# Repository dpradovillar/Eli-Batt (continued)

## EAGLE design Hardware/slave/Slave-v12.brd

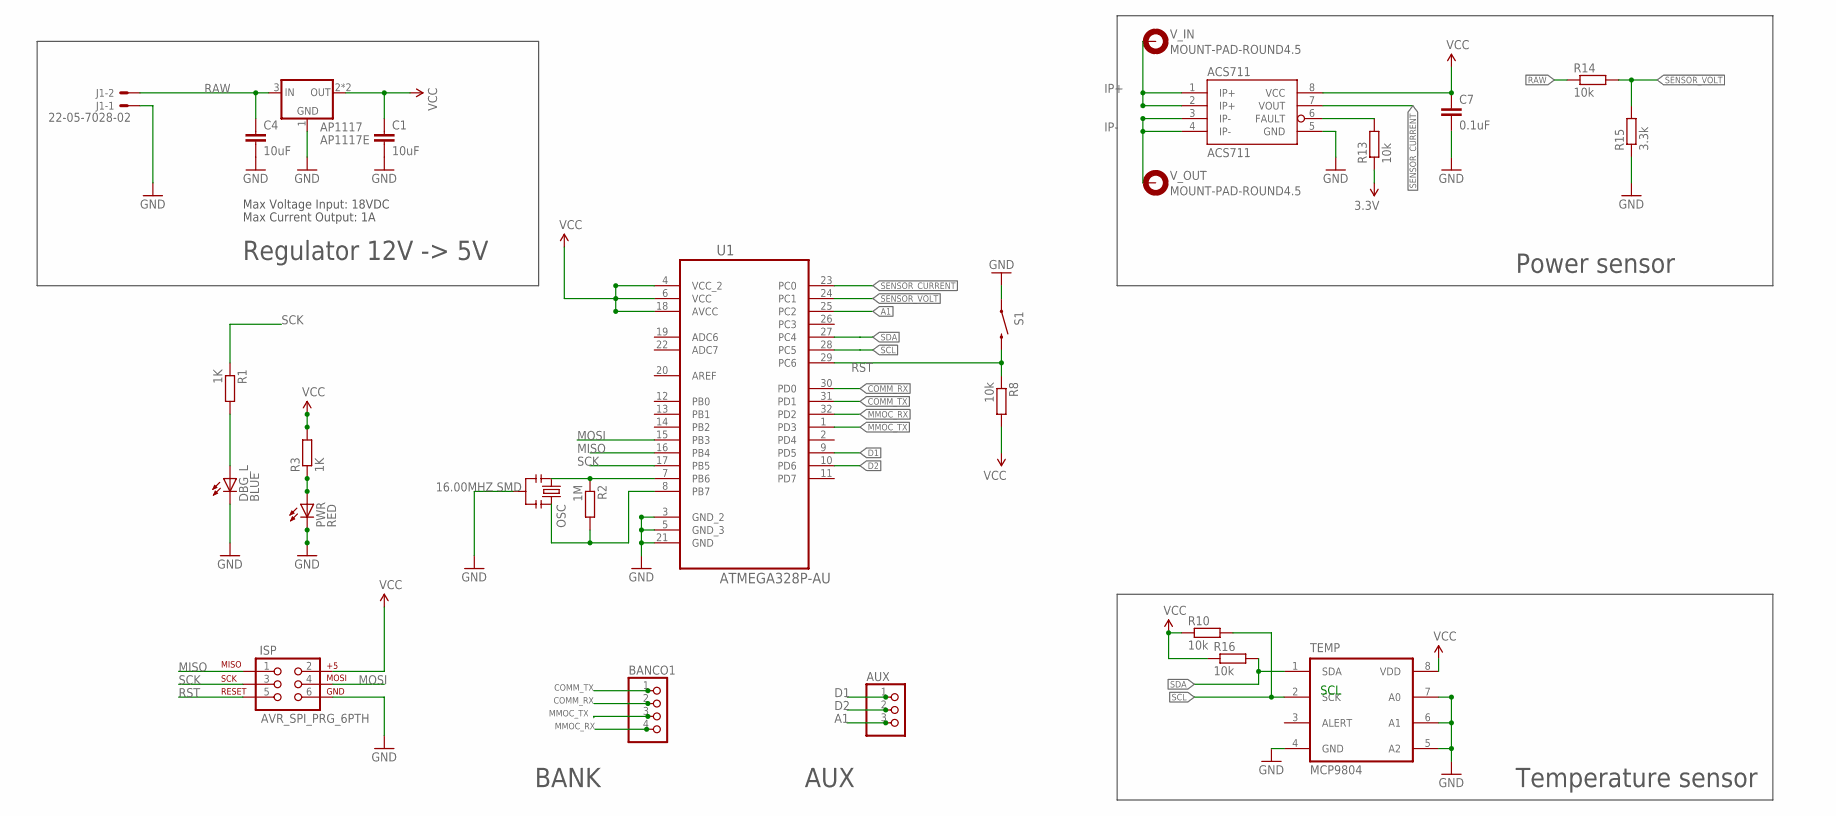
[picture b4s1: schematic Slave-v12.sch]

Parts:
ACS711: ACS711; SOIC8; MPN ACS711KLCTR-25AB-T
AP1117: AP1117E; SOT223; MPN AP1117E50G-13
AUX: PINHD-1X3; 1X03
BANCO1: PINHD-1X4; 1X04
C1, C4: 10uF; C0805K; MPN 0805ZD106KAT2A
C7: 0.1uF; C0805K; MPN MC0603B104K500CT
DBG_L: BLUE; CHIPLED_0805; MPN 150080BS75000
ISP: AVR_SPI_PRG_6PTH; 2X3
J1: 22-05-7028-02; 7395-02
OSC: 16.00MHZ SMD; RESONATOR-SMD; MPN PBRC8.00HR50X000
PWR: RED; CHIPLED_0805; MPN KPT-2012SRC-J4
R1, R3: 1K; R0805; MPN CRCW08051K00FKTA
R2: 1M; R0805; MPN CRCW080510K0FKTA
R8, R10, R13, R14, R16: 10k; R0805; MPN CRCW080510K0FKTA
R15: 3.3k; R0805; MPN CRCW08053K30FKTA
S1: SWITCH-MOMENTARY-2-SMD-1101NE; TACTILE-SWITCH-1101NE
TEMP: MCP9804; MSOP8; MPN MCP9808-E/MS
U1: ATMEGA328P-AU; QFP80P900X900X120-32N
V_IN: MOUNT-PAD-ROUND4.5; 4,5-PAD
V_OUT: MOUNT-PAD-ROUND4.5; 4,5-PAD

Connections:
A1: AUX.3, U1.25 (PC2)
COMM_RX: BANCO1.2, U1.30 (PD0)
COMM_TX: BANCO1.1, U1.31 (PD1)
D1: AUX.1, U1.9 (PD5)
D2: AUX.2, U1.10 (PD6)
GND: ACS711.5 (GND), AP1117.1 (GND), C1.2, C4.2, C7.2, DBG_L.C, ISP.6, J1.1, OSC.2, PWR.C, R15.1, S1.P$1 (1), TEMP.4 (GND), TEMP.5 (A2), TEMP.6 (A1), TEMP.7 (A0), U1.3 (GND_2), U1.5 (GND_3), U1.21 (GND)
IP+: ACS711.1 (IP+), ACS711.2 (IP+), V_IN.B4,5
IP-: ACS711.3 (IP-), ACS711.4 (IP-), V_OUT.B4,5
MISO: ISP.1, U1.16 (PB4)
MMOC_RX: U1.32 (PD2)
MMOC_TX: BANCO1.3, U1.1 (PD3)
MOSI: ISP.4, U1.15 (PB3)
unnamed: OSC.1, R2.1, U1.7 (PB6)
unnamed: DBG_L.A, R1.2
unnamed: PWR.A, R3.1
unnamed: OSC.3, R2.2, U1.8 (PB7)
unnamed: ACS711.6 (FAULT), R13.2
RAW: AP1117.3 (IN), C4.1, J1.2, R14.1
RST: ISP.5, R8.1, S1.P$2 (2), U1.29 (PC6)
SCK: ISP.3, R1.1, U1.17 (PB5)
SCL: R10.2, TEMP.2 (SCK), U1.28 (PC5)
SDA: R16.2, TEMP.1 (SDA), U1.27 (PC4)
SENSOR_CURRENT: ACS711.7 (VOUT), U1.23 (PC0)
SENSOR_VOLT: R14.2, R15.2, U1.24 (PC1)
VCC: ACS711.8 (VCC), AP1117.2 (OUT), AP1117.4 (OUT), C1.1, C7.1, ISP.2, R3.2, R8.2, R10.1, R13.1, R16.1, TEMP.8 (VDD), U1.4 (VCC_2), U1.6 (VCC), U1.18 (AVCC)

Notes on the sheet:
Max Voltage Input: 18VDC
Max Current Output: 1A
Regulator 12V -> 5V
Power sensor
Temperature sensor
SCL
BANK
AUX

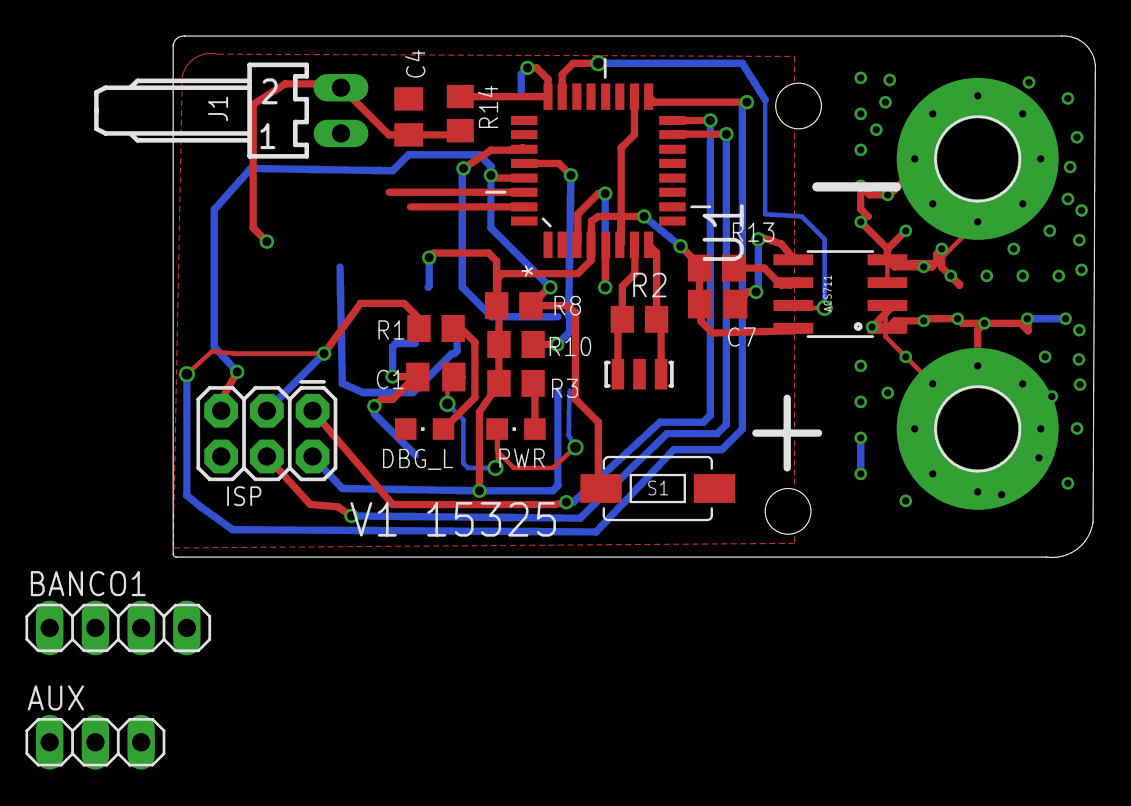
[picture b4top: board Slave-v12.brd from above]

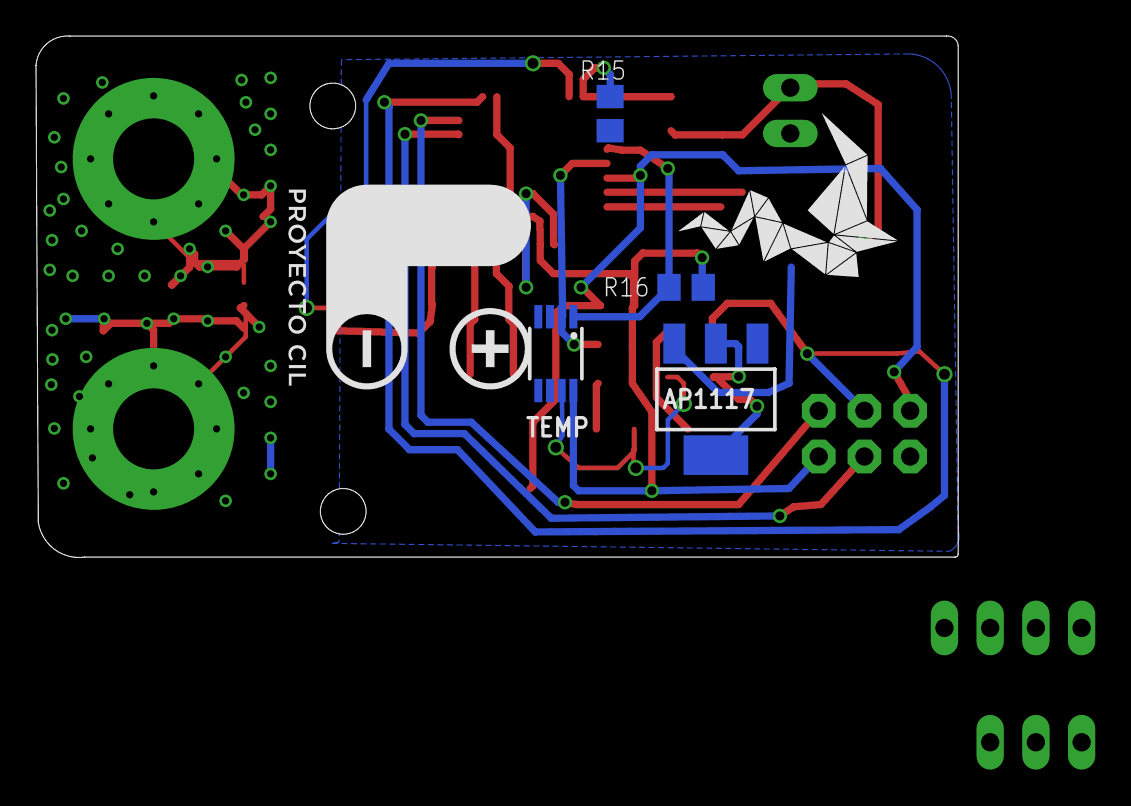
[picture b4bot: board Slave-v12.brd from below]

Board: 2 copper layers, 51.2 x 29.0 mm, 28 parts (6 on the bottom side), 24 nets.

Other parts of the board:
U$1: LOGO_CIL
U$4: LOGO_ELIBATT2

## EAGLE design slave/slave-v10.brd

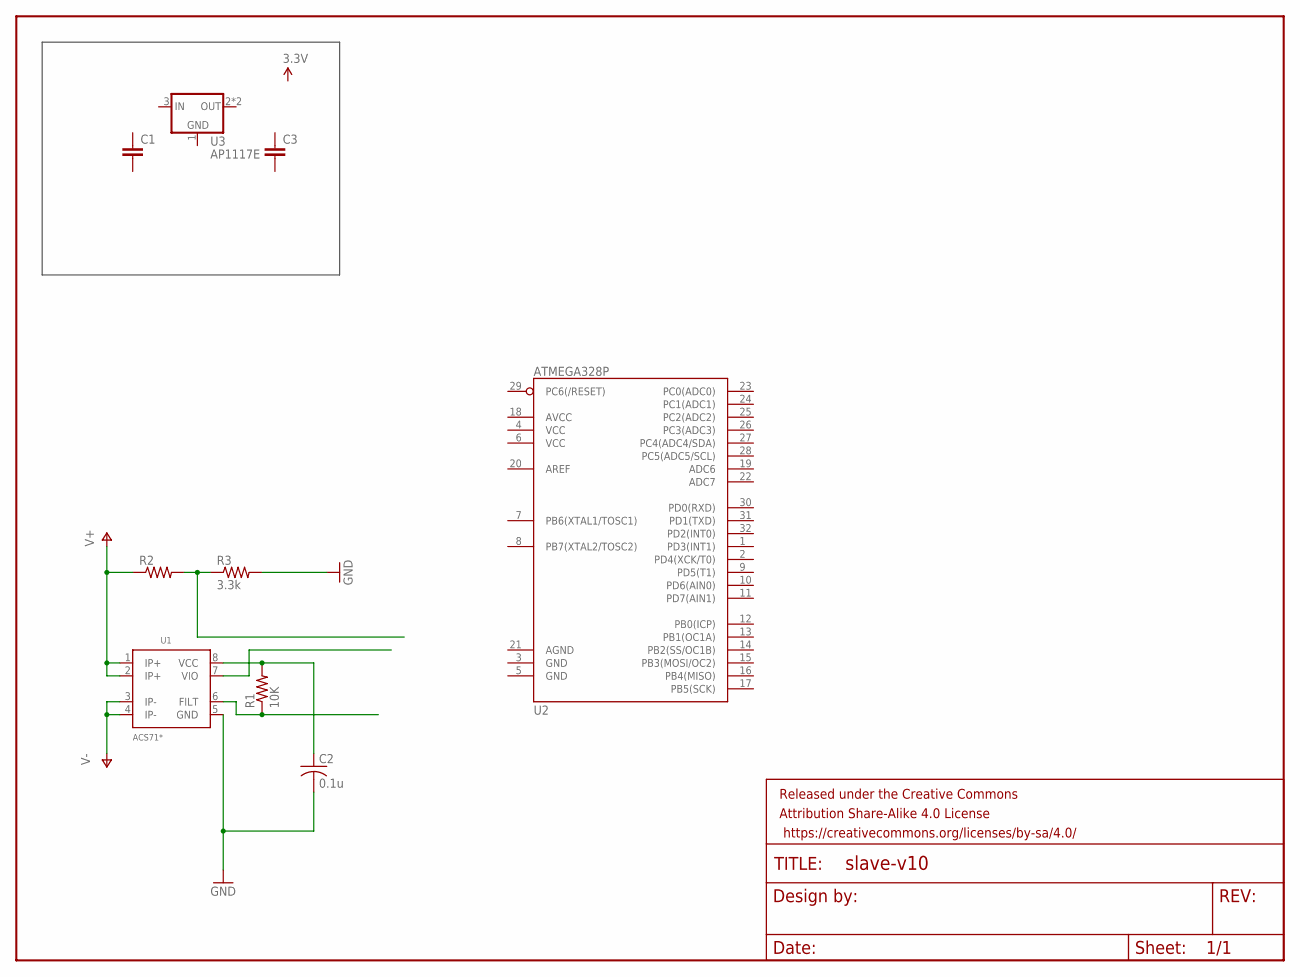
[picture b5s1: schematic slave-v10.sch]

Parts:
C1, C3: CAP0805; 0805
C2: 0.1u; C0603; PARTNO CC0603MRY5V9BB104
FRAME1: FRAME-LETTER; CREATIVE_COMMONS
R1: 10K; R0603; PARTNO RMCF0603FT10K0
R2: 10k; R0603; PARTNO ERJ-3EKF3302V
R3: 3.3k; R0603; PARTNO RMCF0603FT10K0
U1: ACS71*; SO08; PARTNO ACS715ELCTR-20A-T
U2: ATMEGA328P; TQFP32-08
U3: AP1117E; SOT223

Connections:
5V: C2.1, R1.2, U1.8 (VCC)
GND: C2.2, R3.2, U1.5 (GND)
unnamed: R1.1, U1.6 (FILT)
V+: R2.1, U1.1 (IP+), U1.2 (IP+)
V-: U1.3 (IP-), U1.4 (IP-)
VSENSE: R2.2, R3.1

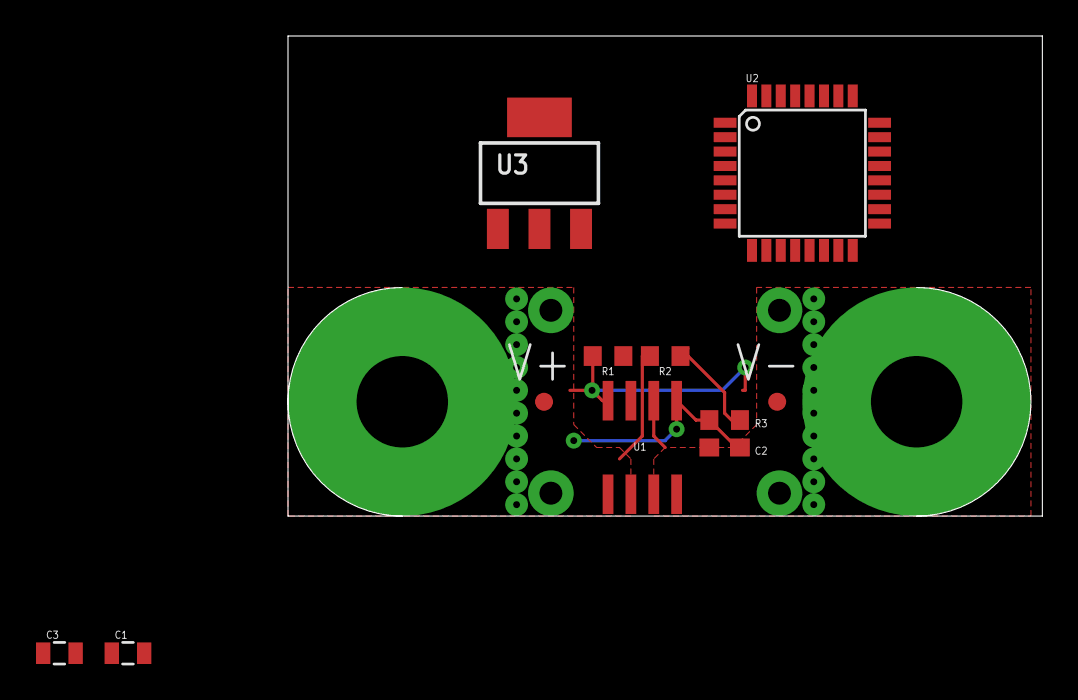
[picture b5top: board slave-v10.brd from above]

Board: 2 copper layers, 41.9 x 26.7 mm, 12 parts (0 on the bottom side), 6 nets.

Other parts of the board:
U$1, U$2: FIDUCIAL_G10

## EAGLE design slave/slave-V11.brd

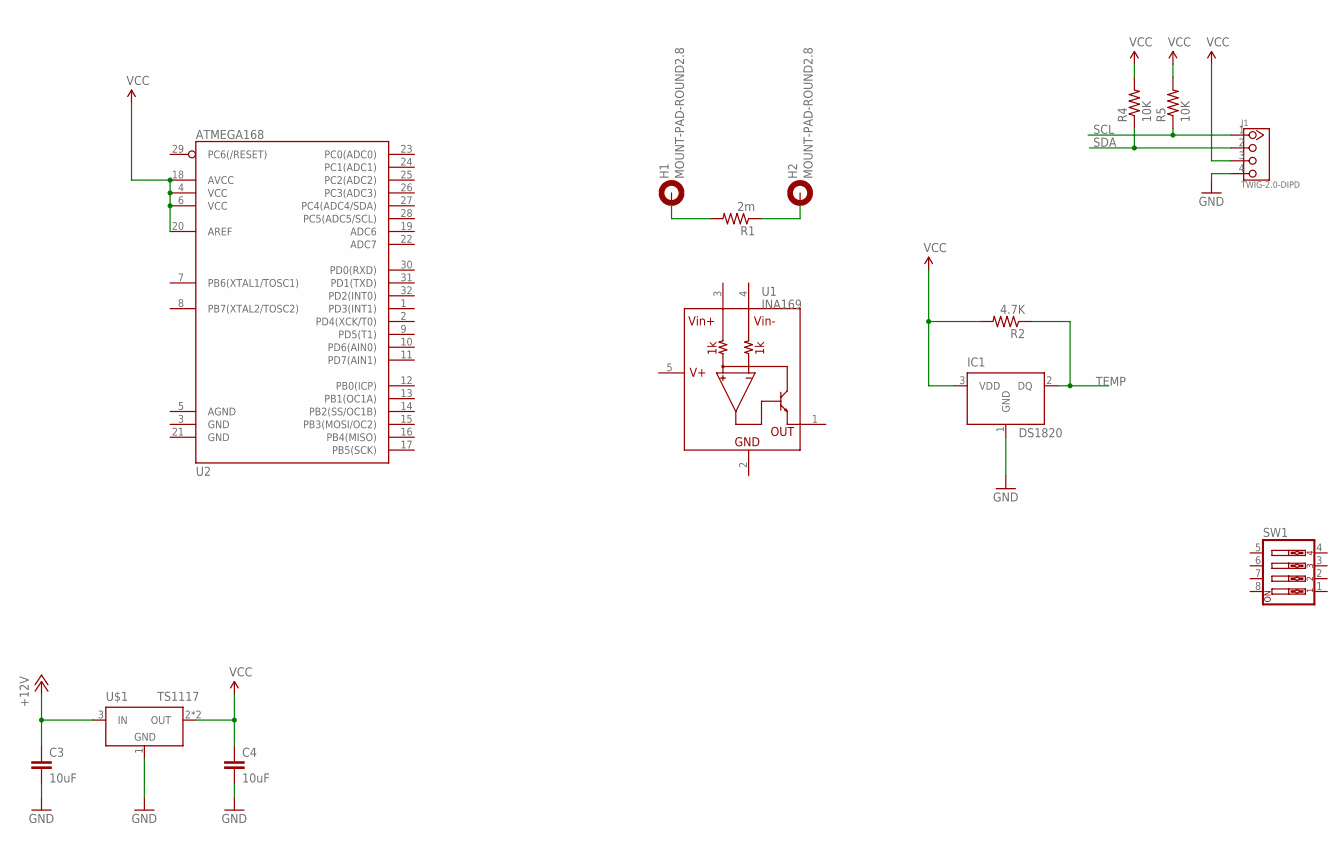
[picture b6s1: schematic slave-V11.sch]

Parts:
C3, C4: 10uF; 0805
H1, H2: MOUNT-PAD-ROUND2.8; 2,8-PAD
IC1: DS1820; TO-92
J1: TWIG-2.0-DIPD; 2.0_1X4_90
R1: 2m; R2512
R2: 4.7K; 0805
R4, R5: 10K; 0805
SW1: SW_DIP-4; EDG-04
U1: INA169; SOT23-5
U2: ATMEGA168; TQFP32-08
U$1: TS1117; SOT223

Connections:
+12V: C3.1, U$1.3 (IN)
GND: C3.2, C4.2, IC1.1 (GND), J1.4, U$1.1 (GND)
SCL: J1.1, R5.1
SDA: J1.2, R4.1
TEMP: IC1.2 (DQ), R2.1
VCC: C4.1, IC1.3 (VDD), J1.3, R2.2, R4.2, R5.2, U2.4 (VCC), U2.6 (VCC), U2.18 (AVCC), U2.20 (AREF), U$1.2 (OUT), U$1.4 (OUT)
VIN+: H1.B2,8, R1.2
VIN-: H2.B2,8, R1.1

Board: 2 copper layers, 14 parts (0 on the bottom side), 8 nets, no tracks yet.

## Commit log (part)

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2014-06-12 primer git
2014-06-12 segundo git
2014-06-12 Primer diseño PCB Slave
2014-06-27 a new master was born
2014-06-27 SD + Atmega1280 + reg5V
2014-07-01 Faltan cosas
2014-07-01 fix RESET pin
2014-07-02 Avanzado diagrama de la parte del ft232.
2014-07-02 Conector USBMini
    Es más resistente que el USBmicro mecanicamente. El usb normal exije un
    cable no tan standar
2014-07-04 todos los componentes V10
    Falta revisar compatibilidad entre modulos y hacer layout
2014-07-14 add sensor eagle lbr
2014-07-14 add grove connector eagle lbr
2014-07-14 avanzado temperatura y otros
2014-07-15 agregado comunicacion
2014-07-15 add resonator
2014-07-15 12DC Power Connector and 1st layout
2014-07-15 agregados archivos temporales al ignore list
2014-07-15 agregados pads
2014-07-15 actualizado brd, y arreglado tamaño de algunos componentes
2014-07-15 orden en esquematico
2014-07-15 some trace route
2014-07-16 more traces
2014-07-16 casi todas las pistas
    FALTA!! Revisar que no hayan circulos en circuitos de potencia y agregar
    pistas sensor corriente.
2014-07-17 archivos temp de forma generica al ignore list
2014-07-17 Corregdas pistas, corregido error en la pila del RTC
2014-07-17 modelo 3d
2014-07-17 Agrandada pista de corriente
2014-07-18 Revert "."
    This reverts commit a0e0a30c928bb4e20c64730e80fb18a043fca9c0.
2014-07-18 Ajustado silk Screen
2014-07-18 elimindos archivos inutiles
2014-07-18 Gerbers
2014-07-18 render
2014-07-22 add reset button
    and rounded corners
2014-07-22 release for manufacture
    gerbers with logo and renders
2014-07-23 fix gnd for PWR LED and update gerbers with logos
2014-07-24 gerbers fix
    add current sensor cupper area to the soldermask
2014-07-28 add AUX Current sensor
2014-07-30 Revert "."
    This reverts commit 88ed2cc015553062a76e2134231f87feefea0a33.
2014-07-31 render
    PCB Black
2014-08-02 gerbes + BOM
    add more tweaks
2014-08-30 Movido a carpeta Hardware, creada carpeta vacia Firmware
2014-08-30 Probando otro usuario
2014-08-30 Agrega estructura a carpeta Firmware.
    Se colocan librerias en carpeta libraries.
    Se crean dos scripts principales, uno para master y uno para slave.
    Se crea carpeta de pruebas, con los .ino que utilizan las librerias (similar a firmware_master y firmware_slave)
    Falta crear libreria firmware.h que contendra las definiciones de master y slave, para usar en los .ino de firmware.
2014-08-31 Agrega definicion de clases para firmware de master y slave.
    Falta agregar los metodos.
2014-08-31 Agrega librerias utilitarias para construccion de firmware.
    - Agrega EepromId, que maneja los ids unicos escritos en la eeprom de la tarjeta.
    - Agrega SampleCollector, que permite obtener datos y ejecutar acciones a uan frequencia determinada.
    - Agrega SimpleCrc, que permite construir checksums para validar contenidos de datos.
2014-08-31 Corrige readme.txt
2014-09-02 Se inician pruebas de librerias (se usan los Firmware* para este fin).
    - Se mueve SoftwareSerial a libraries (se agrega constructor vacio, por
    conveniencia para Elibatt)
    - Se agrega la nueva libreria DataExchanger para intercambio de mensajes
    entre tarjetas slave, y master/slave.
    - Se agrega libreria DataStream para envio de datos complejos.
    - Se actualiza EepromId.
2014-09-02 Se termina de implementar comunicacion para Elibatt. Faltan pruebas.
    Se completa DataExchanger.
    - Falta incluir mecanismo de timeout.
    - Falta includeir mecanismo de acknowledgement.
    - Corregido multiples bugs.
    - Falta terminar de documentar.
    - Falta manejar errores de funcionamiento (se desconecta un Slave en
2014-09-02 BOM actualizado + cambio de R en FAULT
2014-09-03 Comunicacion terminada y testeada.
    Faltan aun funcionalidades menores.
2014-09-05 Se agrega prueba de sensores analogos e i2c (temperatura).
    Se crea libreria I2cInput para manejo de sensores i2c (en particular, el de temperatura).
    Se crea libreria AnalogInput para manejo de sensores analogos (en particular, el de corriente y voltaje).
    Se agrega libreria de Adafruit modificada, dependencia de mcp9808.
2014-09-05 Se agrega version 0.1 compilada para windows. Se agregan DLLs de Qt necesarias para deploy.
2014-09-05 Se agrega proyecto Website y ServoController.
    Website es el sitio web interno j2ee para publicacion de datos y generacion de reportes.
    ServoController es un proyecto de prueba para comunicacion bluetooth-android.
2014-09-07 Agrega libreria para escribir datos a tarjeta SD (falta refactorizar e implementar).
2014-09-08 Se completan clases para escritura en SD.
    Falta volcar datos, de sensores genericos a SD.
    Se corrigen bugs menores y se agrega documentacion.
    TODO(rtapiapincheira): renombrar eepromId y agregar soporte para escribir
    otras variables en la eeprom.
2014-09-11 Se mejora comunicacion entre tarjetas esclavo/maestro.
    Se agrega software para prueba de GPS.
    Se agrega libreria Debugger para crear traza de logs.
    Se renombra EepromId a EepromWriter.
    Se comienza a implementar logica de FirmwareMaster y FirmwareSlave
    (firmwares definitivos).
    Se completa un poco mas software para configuracion de tarjetas.
2014-09-12 Se corrigen errores de include, se trabaja en protocolo master/slave.
    Falta probar.
    Se mejoran los .ino de prueba de firmware master/slave.
    Se mejora .ino de prueba eeprom.
    Se agregan funciones utilitarias.
    Se modifica clase de sensor de temperatura para enviar datos digitales.
    Se corrige el setup de firmware master/slave (no se iniciaban las comms).
2014-09-18 Trabajo en progreso, comunicacion master/slave. Se mejora interfaz gracica, se agrega soporte para BT.
    - Se agrega libreira AltSoftSerial (dependencia de BLE).
    - Se agrega libreria RedBearLab BLEmini.
    - Se completa interfaz grafica de aplicación Qt (quedan pendientes varias
    funcionalidades).
    - Se agrega release 0.9 de aplicacion Qt para windows.
2014-09-19 Se renombra libreria RBL_BLEMini y se modifica para funcionar con Elibatt.
    Se agrega soporte para tarjeta master (atmega1280).
2014-09-20 Refactoring mayor, que incluye escritura sincronizada de SD.
    - Se borran .ino de Firmware Master/Slave (usar pruebas/pruebaFirmware<Master|Slave>).
    - Se agrega modelo de boards.txt (modificar boards.txt original).
    - Se agrega configuracion de pins y de firmware en elibatt_config.h (ver pin-mapping.pdf).
    - Se quita uso de herencia en clases (problemas de ram en uno, falta revisar uso de ram, mega funciona OK).
    - Se agregan funciones convenientes en Debugger y Utils.
    - Se agrega escritura sincronizada de N slaves en master.
2014-09-23 algunos codigos para prueba
2014-09-27 Trabajo en progreso.
2014-09-28 Trabajo en progreso.
    - Se remueve codigo duplicado en FirmwareMaster/FirmwareSlave.
    - Se agrega clase base Firmware
    - Se reordenan archivos para tener menos librerias, pero con mas clases
    c/u.
2014-09-28 Trabajo en progreso.
    Se refactoriza gran parte de la aplicacion.
    Se avanza en comunicacion master-slave.
2014-09-28 Trabajo en progreso (aun).
2014-09-30 Se incluye Aplicacion Celular que corre Unix test.
    Se modifica unix test para operar por el puerto BLE de master.
2014-10-02 Se optimizan strings literales usando macro F("").
2014-10-05 Se agrega libreria para comunicacion serial.
2014-10-11 Version estable de comunicacion master-slave-pc.
    Se agrega aplicacion simple de consola que implementa comunicacion.
    Se agrega soporte para rtc (para buses i2c malos, se maneja gracefully).
2014-10-14 Se agrega soporte para GPS y BLE.
    Se modifica firmware master para dividir comunicacion.
    Se modifica app android para recepcion de paquetes binarios.
2014-10-14 Se agrega BLE y SD a pruebaSensors.
2014-10-16 fix RTC and Temp wires
    In schematic
2014-10-18 Actualizacion de app android.
2014-10-20 Versión 1.0 de Elibatt-Console.
2014-11-25 V12
    corrección Labels y pistas
2014-12-18 BOM Master V12 + gerbers
2015-03-27 V12
    V12 de Master y slave, con gerbers y BOM
2015-04-28 Re incorporacion de librerias en repo GitHub.
2015-04-30 Corrección menor que permite usar BLE.
2015-04-30 Correcciones varias.
    - Mejora formateo de fechas/horas.
    - Agrega prueba aislada de modulo BLE.
    - Corrige detalles en prueba aislada de GPS.
    - Corrige detalles menores en prueba aislada de RTC.
    - Corrige detalles menores en prueba aislada de SD.
    - Agrega prueba aislada de sensor de temperatura.
2015-05-04 Actualización de librería de temperatura.
2015-05-04 Correcciones varias.
    - Se agrega soporte para escritura de floats en librería de SdData.
    - Se agregan parametros float para debugeo en estructura GpsStruct (si se necesitan enviar, se puede usar la parte entera/decimal, que son enteros).
    - Se actualiza firmware (V2Libs.h) para usar escritura en SD y RTC.
    - Se renombran métodos, variables y se limpia en general.
    - Se agrega prueba específica para testar SD/Temperatura (combinación conflictiva).
2015-05-04 Trabajo en progreso (don't merge into master). Se actualiza librería de RTC y se crea prueba minima para ejecutar sd+rtc+mcp9808.
    La librería de RTC actualizada desde Adafruit introduce cambios mayores y requiere ser adaptado el código de elibatt.
2015-05-04 Se modifica tiempo de volcado a archivo (cada 15min).
2015-05-05 Agrega nueva librería para uso de RTC (DS3231).
2015-05-05 Modificación de librería OneWire para ser usada en el proyecto.
2015-05-05 Agrega librería de SD de Adafruit (wrapper de sdfat) y modificada para que no crashee con la SD de Arduino.
2015-05-07 Agrega script para generar proyecto para editar en QtCreator.
2015-05-07 INCOMPLETO. Modifica RtcInput para usar la librería del DT3231 antigua nuevamente.
2015-05-14 Actualiza sketch para asignar ID únicos escritos en eeprom.
2015-05-24 Integra aplicación Android exclusiva para renombramiento de la conexión BLE.
2015-05-24 Cambios y correcciones menores para prueba de nuevos sensores en placa con jumpers.
2015-06-04 Implementada comunicación slave-slave.
    - Los comandos ('T', 'C', 'V') se reciben, responden y propagan a través de la cadena de slaves.
    - Las respuestas recibidas de slaves se retropropagan para alcanzar master.
2015-06-09 Respuesta enviada a aplicación móvil ahora incluye el comando usado (i.e para 'T', retorna "T:22.5\n").
2015-06-09 Corrección del protocolo anterior (se agrega prefijo en respuesta para variables de GPS).
2015-06-09 Agrega test funcional para RTC que usa SPI.
    Falta integrarlo en el firmware.
2015-06-16 Integración inicial de sensores RTC con SPI y DS1820.
2015-06-16 Terminada comunicación slave-slave y master-slave.
    Falta: integracion de sensores.
2015-06-18 Prueba sensor de temperatura dallas ds18B20
2015-06-18 Quita informacion de debug al partir firmware, para evitar posible ruido inicial.
2015-06-18 Agrega libreria DallasTemperature.
2015-06-25 Agrega MCP9808.
2015-06-30 Agrega comando R0/R1 para apagar/prender relé en el pin digital 36 (el led en el pin 13 reflejará el estado high/low de este pin).
2015-07-02 Actualiza aplicación de consola para listar conexiones BLE antes de comunicarse.
2015-07-02 Correcciones menores.
2015-07-02 Se agrega proyecto para control de luces via android. Se agrega flag de status en calculo de variables promedio en master. Se re ajustan valores de divisor de voltaje en master.
2015-07-09 Agrega set de hora/fecha via comando (SDATEyyyyMMddThhmmss y GDATE).
2015-07-14 Corrección en captura de temperatura y estado del relé.
2015-07-24 Agrega versión inicial de Elibatt-Viewer.
2015-07-24 Agrega datos CSV de prueba.
2015-07-30 Agrega marco de primer grafico.
2015-07-30 Se termina la generación de reporte simple a partir de datos de SD.
2015-07-30 Correcciones menores a procesamiento de datos.
    Falta agregar indicador de progreso al procesar archivos (util para grandes cantidades de archivos).
2015-07-30 Agrega ejemplo de reporte PDF generado por la aplicacion.
2015-07-30 Se agrega indicador de progreso de creación de reporte.
2015-07-31 Agrega binario ejecutable final distribuible.
2015-08-03 DLL corregida
2015-08-07 :octocat: Added .gitattributes & .gitignore files
2015-08-07 Eli-Batt
    8-7-15
2015-08-18 v13
    formato itead
